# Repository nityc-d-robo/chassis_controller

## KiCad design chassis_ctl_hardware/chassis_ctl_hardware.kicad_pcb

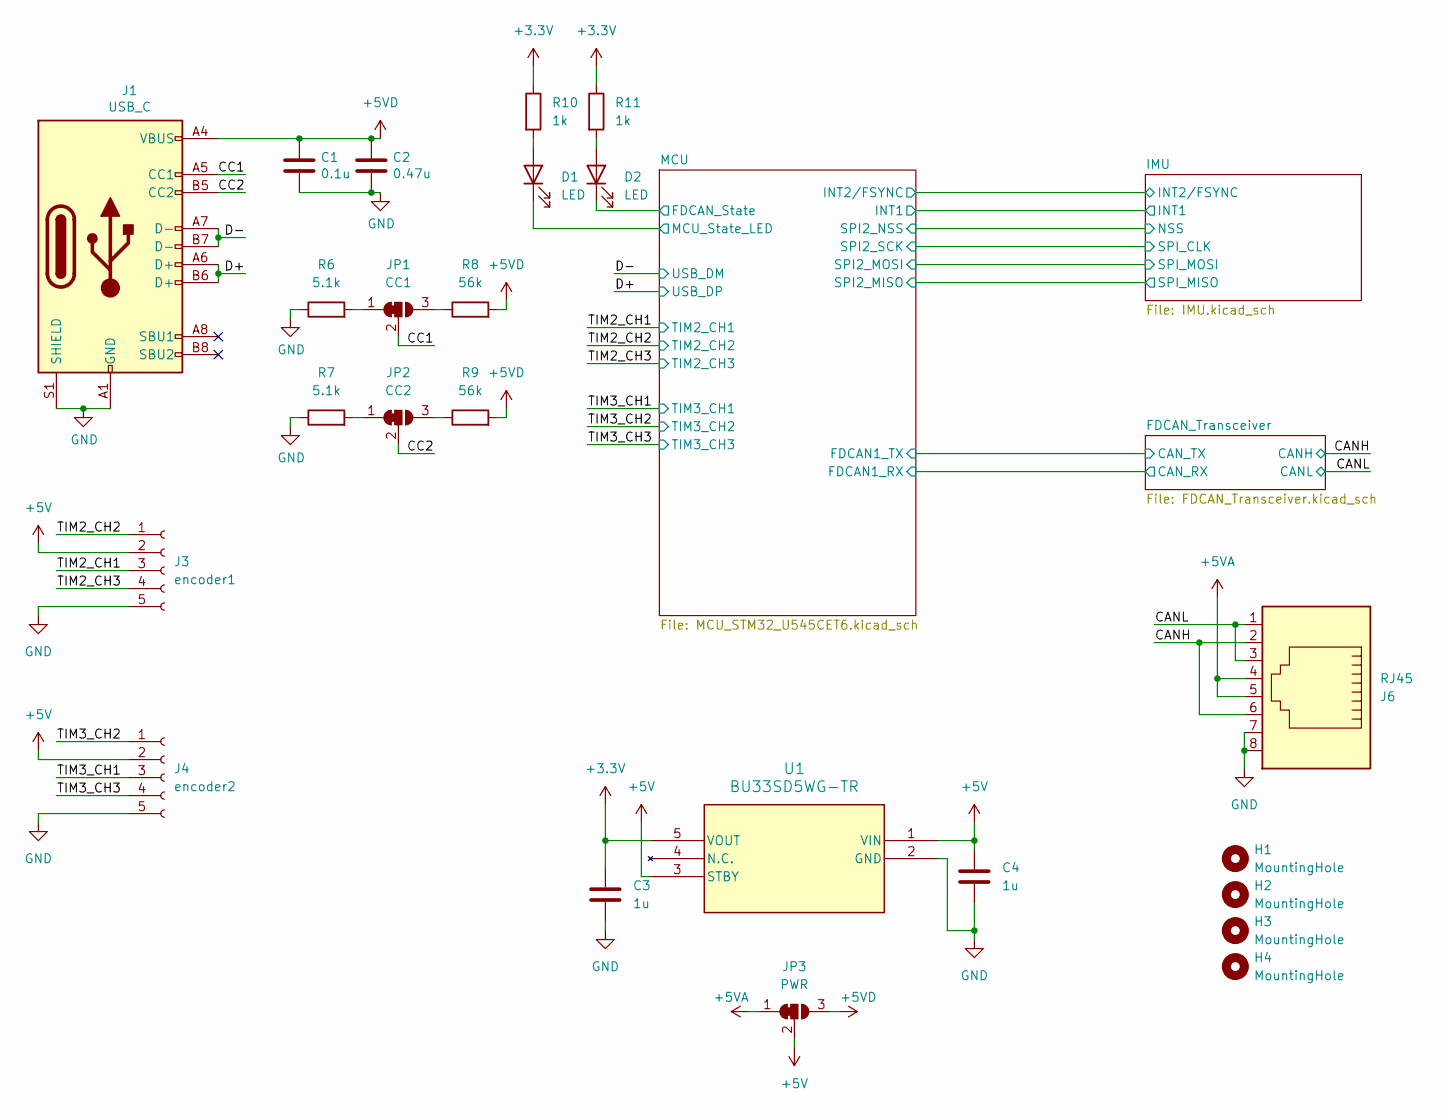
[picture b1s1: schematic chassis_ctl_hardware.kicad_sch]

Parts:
C1: 0.1u; C_0603_1608Metric_Pad1.08x0.95mm_HandSolder
C2: 0.47u; C_0603_1608Metric_Pad1.08x0.95mm_HandSolder
C3, C4: 1u; C_0603_1608Metric_Pad1.08x0.95mm_HandSolder
D1, D2: LED; LED_0603_1608Metric_Pad1.05x0.95mm_HandSolder
H1, H2, H3, H4: MountingHole; MountingHole_3.2mm_M3
J1: USB_C; usb_c
J3: encoder1; JST_XH_S5B-XH-A_1x05_P2.50mm_Horizontal
J4: encoder2; JST_XH_S5B-XH-A_1x05_P2.50mm_Horizontal
J6: RJ45; RJ45_Amphenol_54602-x08_Horizontal
JP1: CC1; SolderJumper-3_P1.3mm_Bridged12_RoundedPad1.0x1.5mm
JP2: CC2; SolderJumper-3_P1.3mm_Bridged12_RoundedPad1.0x1.5mm
JP3: PWR; SolderJumper-3_P1.3mm_Bridged12_RoundedPad1.0x1.5mm
R6, R7: 5.1k; R_0603_1608Metric_Pad0.98x0.95mm_HandSolder
R8, R9: 56k; R_0603_1608Metric_Pad0.98x0.95mm_HandSolder
R10, R11: 1k; R_0603_1608Metric_Pad0.98x0.95mm_HandSolder
U1: BU33SD5WG-TR; SOT95P280X125-5N

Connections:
+3.3V: C3.1, R10.1, R11.1, U1.5 (VOUT); also elsewhere on the board
+5V: C4.1, J3.2, J4.2, JP3.2 (C), U1.1 (VIN), U1.3 (STBY); also elsewhere on the board
+5VA: J6.4, J6.5, JP3.1 (A)
+5VD: C1.1, C2.1, J1.A4 (VBUS), J1.A9 (VBUS), J1.B4 (VBUS), J1.B9 (VBUS), JP3.3 (B), R8.2, R9.2
/CANH: J6.2, J6.6; also elsewhere on the board
/CANL: J6.1, J6.3; also elsewhere on the board
/CC1: J1.A5 (CC1), JP1.2 (C)
/CC2: J1.B5 (CC2), JP2.2 (C)
/D+: J1.A6 (D+), J1.B6 (D+); also elsewhere on the board
/D-: J1.A7 (D-), J1.B7 (D-); also elsewhere on the board
/MCU/FDCAN_State: D2.1 (K); also elsewhere on the board
/MCU/MCU_State_LED: D1.1 (K); also elsewhere on the board
/TIM2_CH1: J3.3; also elsewhere on the board
/TIM2_CH2: J3.1; also elsewhere on the board
/TIM2_CH3: J3.4; also elsewhere on the board
/TIM3_CH1: J4.3; also elsewhere on the board
/TIM3_CH2: J4.1; also elsewhere on the board
/TIM3_CH3: J4.4; also elsewhere on the board
GND: C1.2, C2.2, C3.2, C4.2, J1.A1 (GND), J1.A12 (GND), J1.B1 (GND), J1.B12 (GND), J1.S1 (SHIELD), J3.5, J4.5, J6.7, J6.8, R6.1, R7.1, U1.2 (GND); also elsewhere on the board
unnamed: D1.2 (A), R10.2
unnamed: D2.2 (A), R11.2
unnamed: JP1.1 (A), R6.2
unnamed: JP1.3 (B), R8.1
unnamed: JP2.1 (A), R7.2
unnamed: JP2.3 (B), R9.1

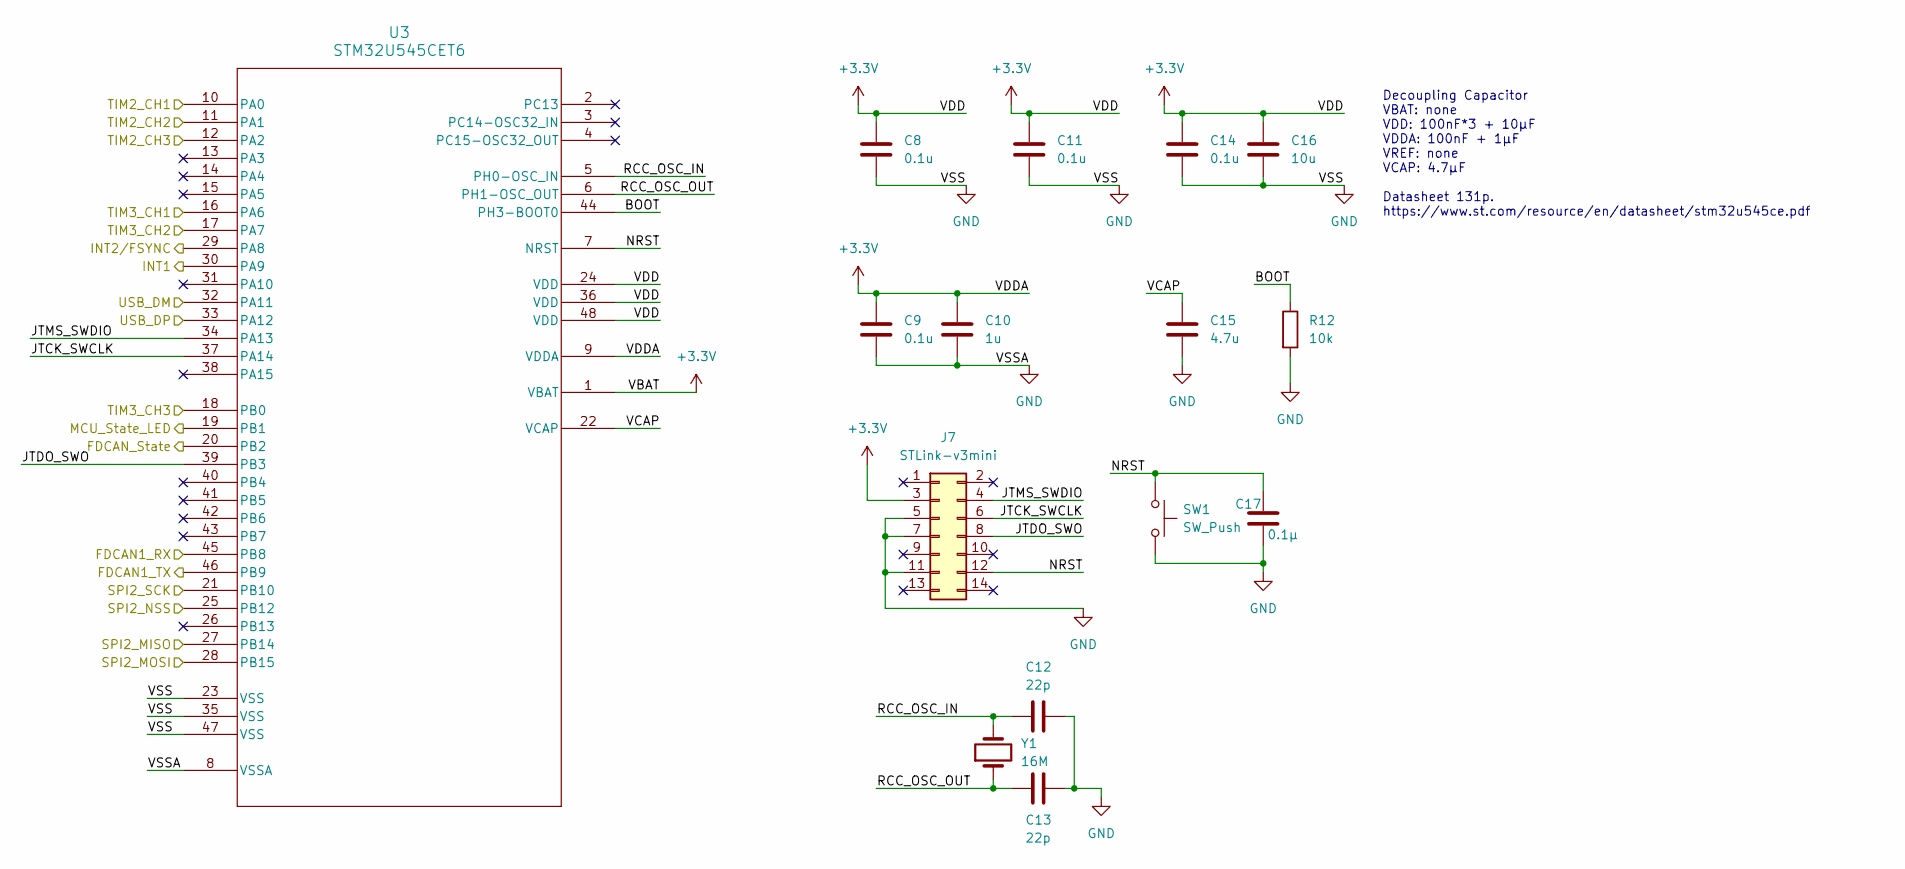
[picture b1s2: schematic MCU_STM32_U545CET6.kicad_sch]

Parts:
C8, C9, C11, C14: 0.1u; C_0603_1608Metric_Pad1.08x0.95mm_HandSolder
C10: 1u; C_0603_1608Metric_Pad1.08x0.95mm_HandSolder
C12, C13: 22p; C_0603_1608Metric_Pad1.08x0.95mm_HandSolder
C15: 4.7u; C_0603_1608Metric_Pad1.08x0.95mm_HandSolder
C16: 10u; C_0603_1608Metric_Pad1.08x0.95mm_HandSolder
C17: 0.1μ; C_0603_1608Metric_Pad1.08x0.95mm_HandSolder
J7: STLink-v3mini; CONN14_3220-14_CNC
R12: 10k; R_0603_1608Metric_Pad0.98x0.95mm_HandSolder
SW1: SW_Push; TVAF06-A020B-R
U3: STM32U545CET6; LQFP-48
Y1: 16M; Crystal_HC49-4H_Vertical

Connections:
+3.3V: C8.1, C9.1, C10.1, C11.1, C14.1, C16.1, J7.3, U3.1 (VBAT), U3.9 (VDDA), U3.24 (VDD), U3.36 (VDD), U3.48 (VDD); also elsewhere on the board
/D+: U3.33 (PA12); also elsewhere on the board
/D-: U3.32 (PA11); also elsewhere on the board
/FDCAN_Transceiver/CAN_RX: U3.45 (PB8); also elsewhere on the board
/FDCAN_Transceiver/CAN_TX: U3.46 (PB9); also elsewhere on the board
/IMU/INT1: U3.30 (PA9); also elsewhere on the board
/IMU/INT2/FSYNC: U3.29 (PA8); also elsewhere on the board
/IMU/SPI_CLK: U3.21 (PB10); also elsewhere on the board
/IMU/SPI_MISO: U3.27 (PB14); also elsewhere on the board
/IMU/SPI_MOSI: U3.28 (PB15); also elsewhere on the board
/MCU/BOOT: R12.1, U3.44 (PH3-BOOT0)
/MCU/FDCAN_State: U3.20 (PB2); also elsewhere on the board
/MCU/JTCK_SWCLK: J7.6, U3.37 (PA14)
/MCU/JTDO_SWO: J7.8, U3.39 (PB3)
/MCU/JTMS_SWDIO: J7.4, U3.34 (PA13)
/MCU/MCU_State_LED: U3.19 (PB1); also elsewhere on the board
/MCU/NRST: C17.1, J7.12, SW1.1, U3.7 (NRST)
/MCU/RCC_OSC_IN: C12.1, U3.5 (PH0-OSC_IN), Y1.2
/MCU/RCC_OSC_OUT: C13.2, U3.6 (PH1-OSC_OUT), Y1.1
/MCU/VCAP: C15.1, U3.22 (VCAP)
/TIM2_CH1: U3.10 (PA0); also elsewhere on the board
/TIM2_CH2: U3.11 (PA1); also elsewhere on the board
/TIM2_CH3: U3.12 (PA2); also elsewhere on the board
/TIM3_CH1: U3.16 (PA6); also elsewhere on the board
/TIM3_CH2: U3.17 (PA7); also elsewhere on the board
/TIM3_CH3: U3.18 (PB0); also elsewhere on the board
GND: C8.2, C9.2, C10.2, C11.2, C12.2, C13.1, C14.2, C15.2, C16.2, C17.2, J7.5, J7.7, J7.11, R12.2, SW1.2, U3.8 (VSSA), U3.23 (VSS), U3.25 (PB12), U3.35 (VSS), U3.47 (VSS); also elsewhere on the board

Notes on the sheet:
Decoupling Capacitor VBAT: none VDD: 100nF*3 + 10μF VDDA: 100nF + 1μF VREF: none VCAP: 4.7μF Datasheet 131p. https://www.st.com/resource/en/datasheet/stm32u545ce.pdf

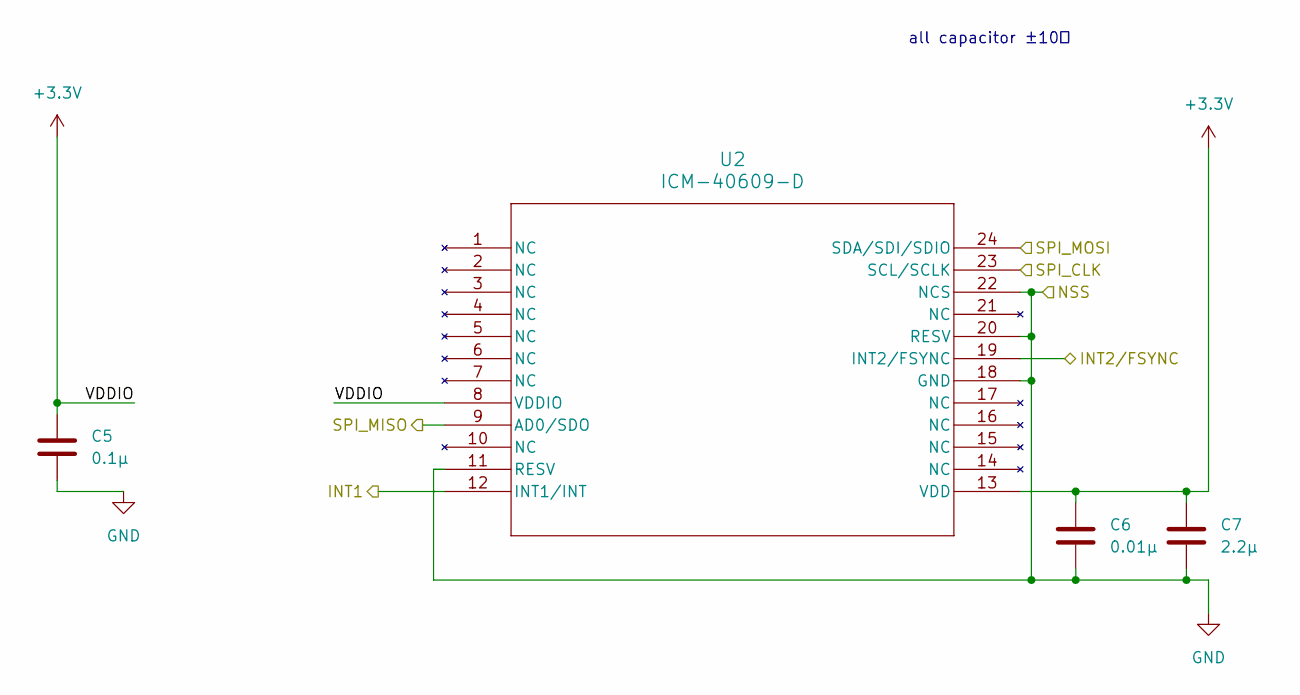
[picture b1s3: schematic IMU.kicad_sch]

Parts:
C5: 0.1μ; C_0603_1608Metric_Pad1.08x0.95mm_HandSolder
C6: 0.01μ; C_0603_1608Metric_Pad1.08x0.95mm_HandSolder
C7: 2.2μ; C_0603_1608Metric_Pad1.08x0.95mm_HandSolder
U2: ICM-40609-D; LGA24_ICM-40609_IVS

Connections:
+3.3V: C5.1, C6.1, C7.1, U2.8 (VDDIO), U2.13 (VDD); also elsewhere on the board
/IMU/INT1: U2.12 (INT1/INT); also elsewhere on the board
/IMU/INT2/FSYNC: U2.19 (INT2/FSYNC); also elsewhere on the board
/IMU/SPI_CLK: U2.23 (SCL/SCLK); also elsewhere on the board
/IMU/SPI_MISO: U2.9 (AD0/SDO); also elsewhere on the board
/IMU/SPI_MOSI: U2.24 (SDA/SDI/SDIO); also elsewhere on the board
GND: C5.2, C6.2, C7.2, U2.11 (RESV), U2.18 (GND), U2.20 (RESV), U2.22 (NCS); also elsewhere on the board

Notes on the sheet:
all capacitor ±10％

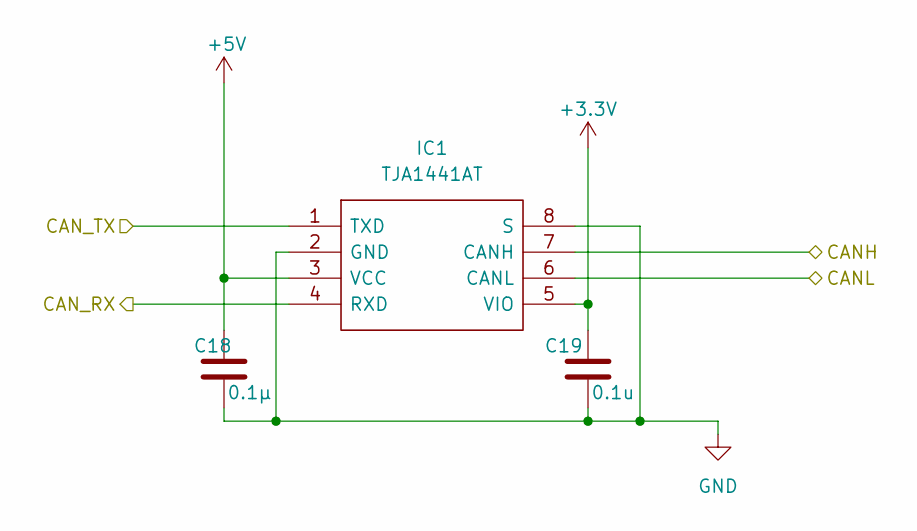
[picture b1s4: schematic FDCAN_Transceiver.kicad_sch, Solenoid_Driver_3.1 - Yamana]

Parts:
C18: 0.1μ; C_0603_1608Metric_Pad1.08x0.95mm_HandSolder
C19: 0.1u; C_0603_1608Metric_Pad1.08x0.95mm_HandSolder
IC1: TJA1441AT; SOIC127P600X175-8N; Manufacturer_Part_Number TJA1441AT

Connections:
+3.3V: C19.1, IC1.5 (VIO); also elsewhere on the board
+5V: C18.1, IC1.3 (VCC); also elsewhere on the board
/CANH: IC1.7 (CANH); also elsewhere on the board
/CANL: IC1.6 (CANL); also elsewhere on the board
/FDCAN_Transceiver/CAN_RX: IC1.4 (RXD); also elsewhere on the board
/FDCAN_Transceiver/CAN_TX: IC1.1 (TXD); also elsewhere on the board
GND: C18.2, C19.2, IC1.2 (GND), IC1.8 (S); also elsewhere on the board

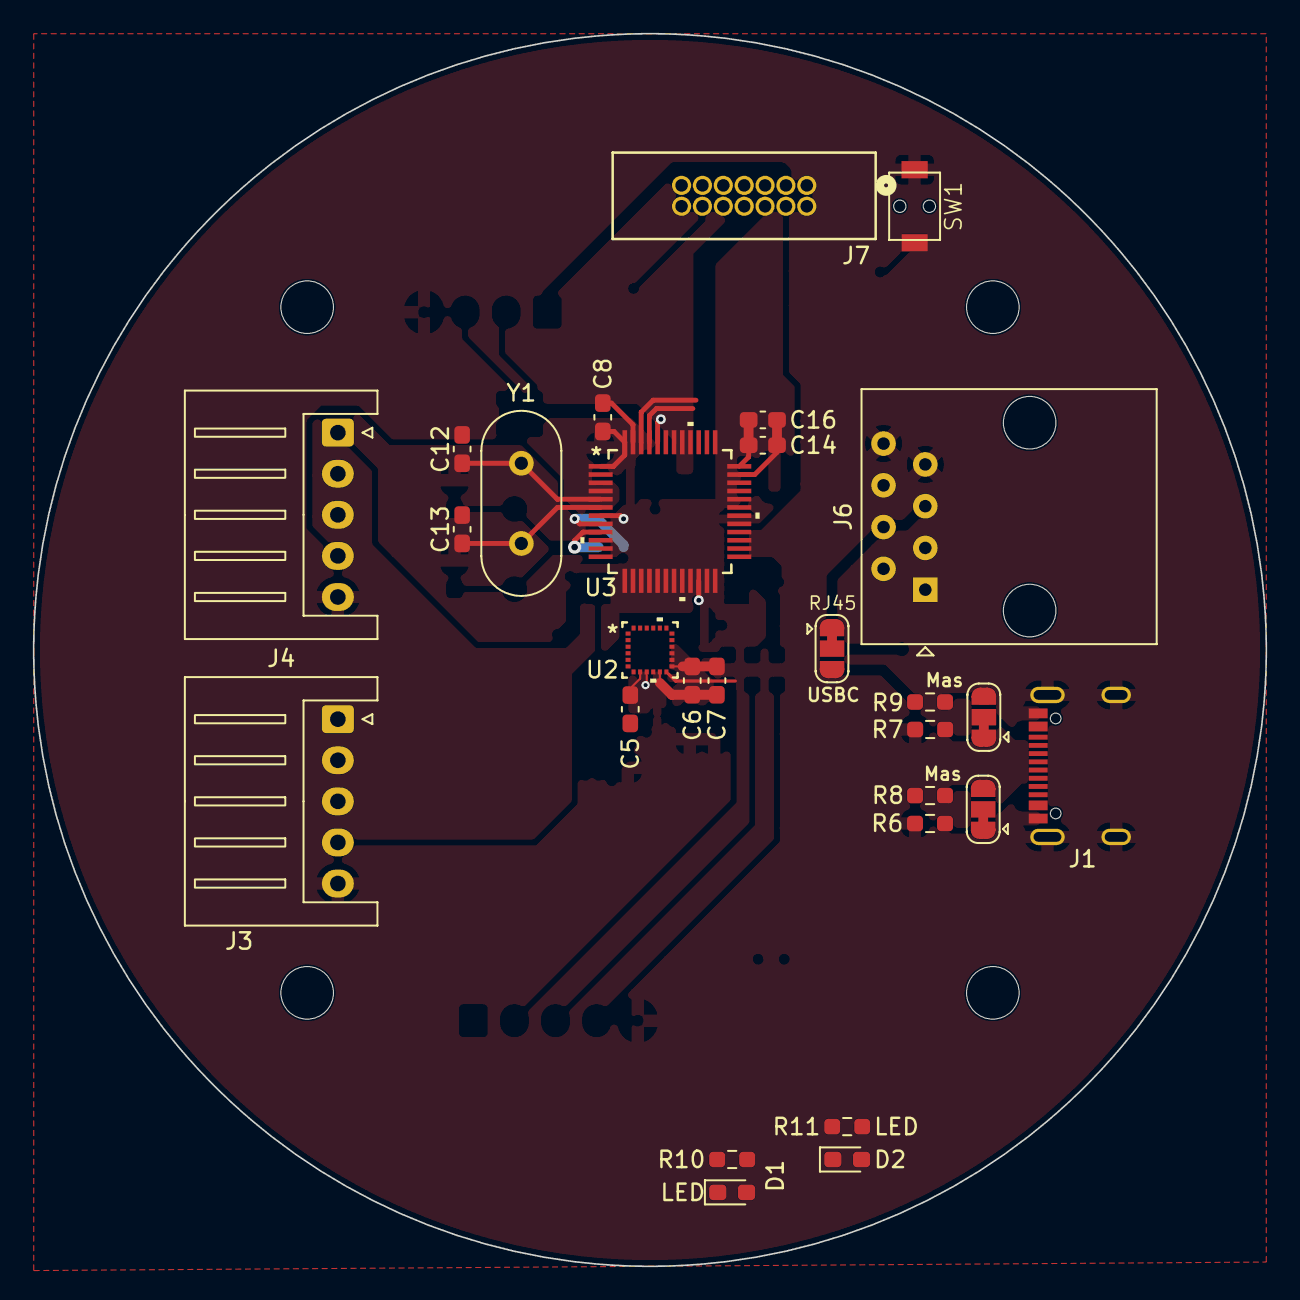
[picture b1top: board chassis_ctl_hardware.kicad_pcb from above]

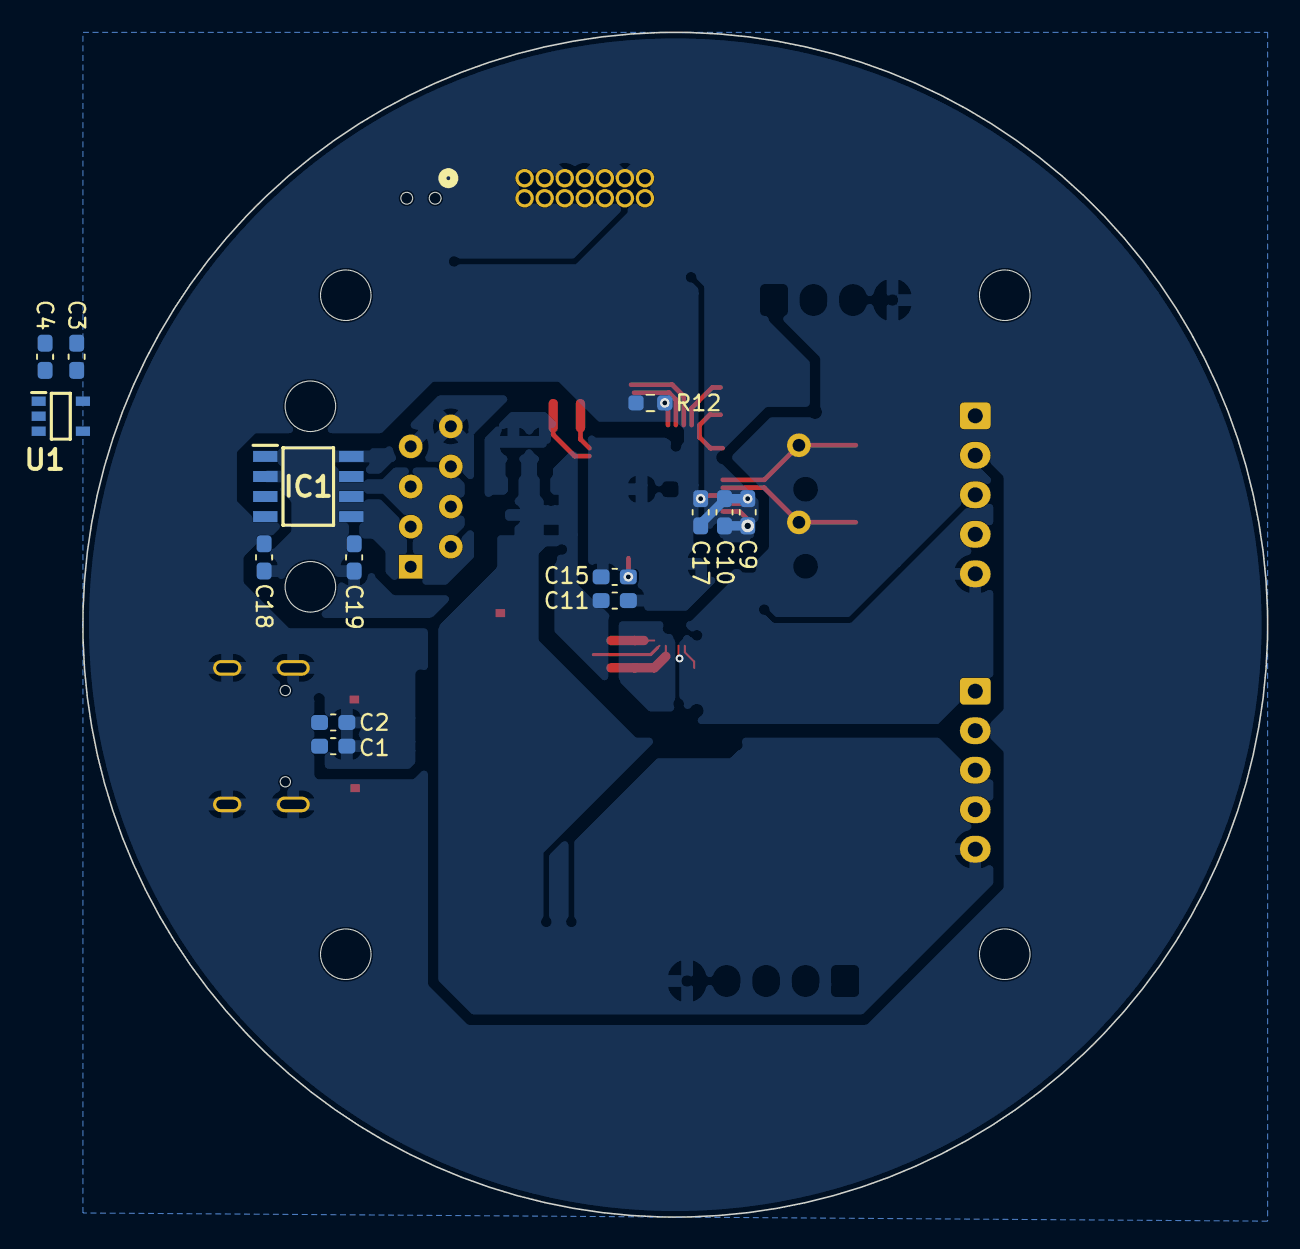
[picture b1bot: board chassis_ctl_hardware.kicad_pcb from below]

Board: 2 copper layers, 75.0 x 75.0 mm, 46 parts (14 on the bottom side), 40 nets.

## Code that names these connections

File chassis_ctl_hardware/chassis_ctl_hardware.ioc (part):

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Mcu.Name=STM32U545CETx
Mcu.Package=LQFP48
Mcu.UserName=STM32U545CETx
PA0.Signal=S_TIM2_CH1
PA1.Signal=S_TIM2_CH2
PA11.Mode=Device
PA11.Signal=USB_DM
PA12.Mode=Device
PA12.Signal=USB_DP
PA13\ (JTMS/SWDIO).Mode=Trace_Asynchronous_SW
PA13\ (JTMS/SWDIO).Signal=DEBUG_JTMS-SWDIO
PA14\ (JTCK/SWCLK).Mode=Trace_Asynchronous_SW
PA14\ (JTCK/SWCLK).Signal=DEBUG_JTCK-SWCLK
PA3.GPIOParameters=GPIO_Label
PA3.GPIO_Label=MCU_State_LED
PA3.Signal=GPIO_Output
PA4.GPIOParameters=GPIO_Label
PA4.GPIO_Label=FDCAN_State
PA4.Signal=GPIO_Output
PA5.Mode=Full_Duplex_Master
PA5.Signal=SPI1_SCK
PA6.Mode=Full_Duplex_Master
PA6.Signal=SPI1_MISO
PA7.Mode=Full_Duplex_Master
PA7.Signal=SPI1_MOSI
PA8.Signal=S_TIM1_CH1
PA9.Signal=S_TIM1_CH2
PB0.GPIOParameters=GPIO_Label
PB0.GPIO_Label=INT2/FSYNC
PB0.Signal=GPXTI0
PB10.Mode=Full_Duplex_Master
PB10.Signal=SPI2_SCK
PB14.Mode=Full_Duplex_Master
PB14.Signal=SPI2_MISO
PB15.Mode=Full_Duplex_Master
PB15.Signal=SPI2_MOSI
PB2.GPIOParameters=GPIO_Label
PB2.GPIO_Label=INT1
PB2.Signal=GPXTI2
PB3\ (JTDO/TRACESWO).Mode=Trace_Asynchronous_SW
PB3\ (JTDO/TRACESWO).Signal=DEBUG_JTDO-SWO
PB6.Mode=I2C
PB6.Signal=I2C1_SCL
PB7.Mode=I2C
PB7.Signal=I2C1_SDA
PB8.Mode=FDCAN_Activate
PB8.Signal=FDCAN1_RX
PB9.Mode=FDCAN_Activate
PB9.Signal=FDCAN1_TX
PC13.Signal=GPXTI13
PH0-OSC_IN\ (PH0).Mode=HSE-External-Oscillator
PH0-OSC_IN\ (PH0).Signal=RCC_OSC_IN
PH1-OSC_OUT\ (PH1).Mode=HSE-External-Oscillator
PH1-OSC_OUT\ (PH1).Signal=RCC_OSC_OUT
RCC.HSE_VALUE=16000000
RCC.SYSCLKFreq_VALUE=48000000
board=custom

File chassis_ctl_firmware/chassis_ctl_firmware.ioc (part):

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Mcu.Name=STM32U545CETx
Mcu.Package=LQFP48
Mcu.UserName=STM32U545CETx
PA0.Signal=S_TIM2_CH1
PA1.Signal=S_TIM2_CH2
PA11.Mode=Device
PA11.Signal=USB_DM
PA12.Mode=Device
PA12.Signal=USB_DP
PA13\ (JTMS/SWDIO).Mode=Trace_Asynchronous_SW
PA13\ (JTMS/SWDIO).Signal=DEBUG_JTMS-SWDIO
PA14\ (JTCK/SWCLK).Mode=Trace_Asynchronous_SW
PA14\ (JTCK/SWCLK).Signal=DEBUG_JTCK-SWCLK
PA15\ (JTDI).Signal=S_TIM2_ETR
PA2.Mode=INP
PA2.Signal=COMP1_INP
PA5.Mode=Full_Duplex_Master
PA5.Signal=SPI1_SCK
PA6.Mode=Full_Duplex_Master
PA6.Signal=SPI1_MISO
PA7.Mode=Full_Duplex_Master
PA7.Signal=SPI1_MOSI
PA8.Signal=S_TIM1_CH1
PA9.Signal=S_TIM1_CH2
PB10.Mode=Full_Duplex_Master
PB10.Signal=SPI2_SCK
PB14.Mode=Full_Duplex_Master
PB14.Signal=SPI2_MISO
PB15.Mode=Full_Duplex_Master
PB15.Signal=SPI2_MOSI
PB3\ (JTDO/TRACESWO).Mode=Trace_Asynchronous_SW
PB3\ (JTDO/TRACESWO).Signal=DEBUG_JTDO-SWO
PB6.Mode=I2C
PB6.Signal=I2C1_SCL
PB7.Mode=I2C
PB7.Signal=I2C1_SDA
PB8.Mode=FDCAN_Activate
PB8.Signal=FDCAN1_RX
PB9.Mode=FDCAN_Activate
PB9.Signal=FDCAN1_TX
RCC.HSE_VALUE=16000000
board=custom
